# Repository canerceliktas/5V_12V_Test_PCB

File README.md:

# 5V_12V_Test_PCB
 Measuring the 2 inputs to detecting correct voltage values and show them on 7-Segment Display using a PIC16F876. It was a control card for measuring our custom design pcbs.

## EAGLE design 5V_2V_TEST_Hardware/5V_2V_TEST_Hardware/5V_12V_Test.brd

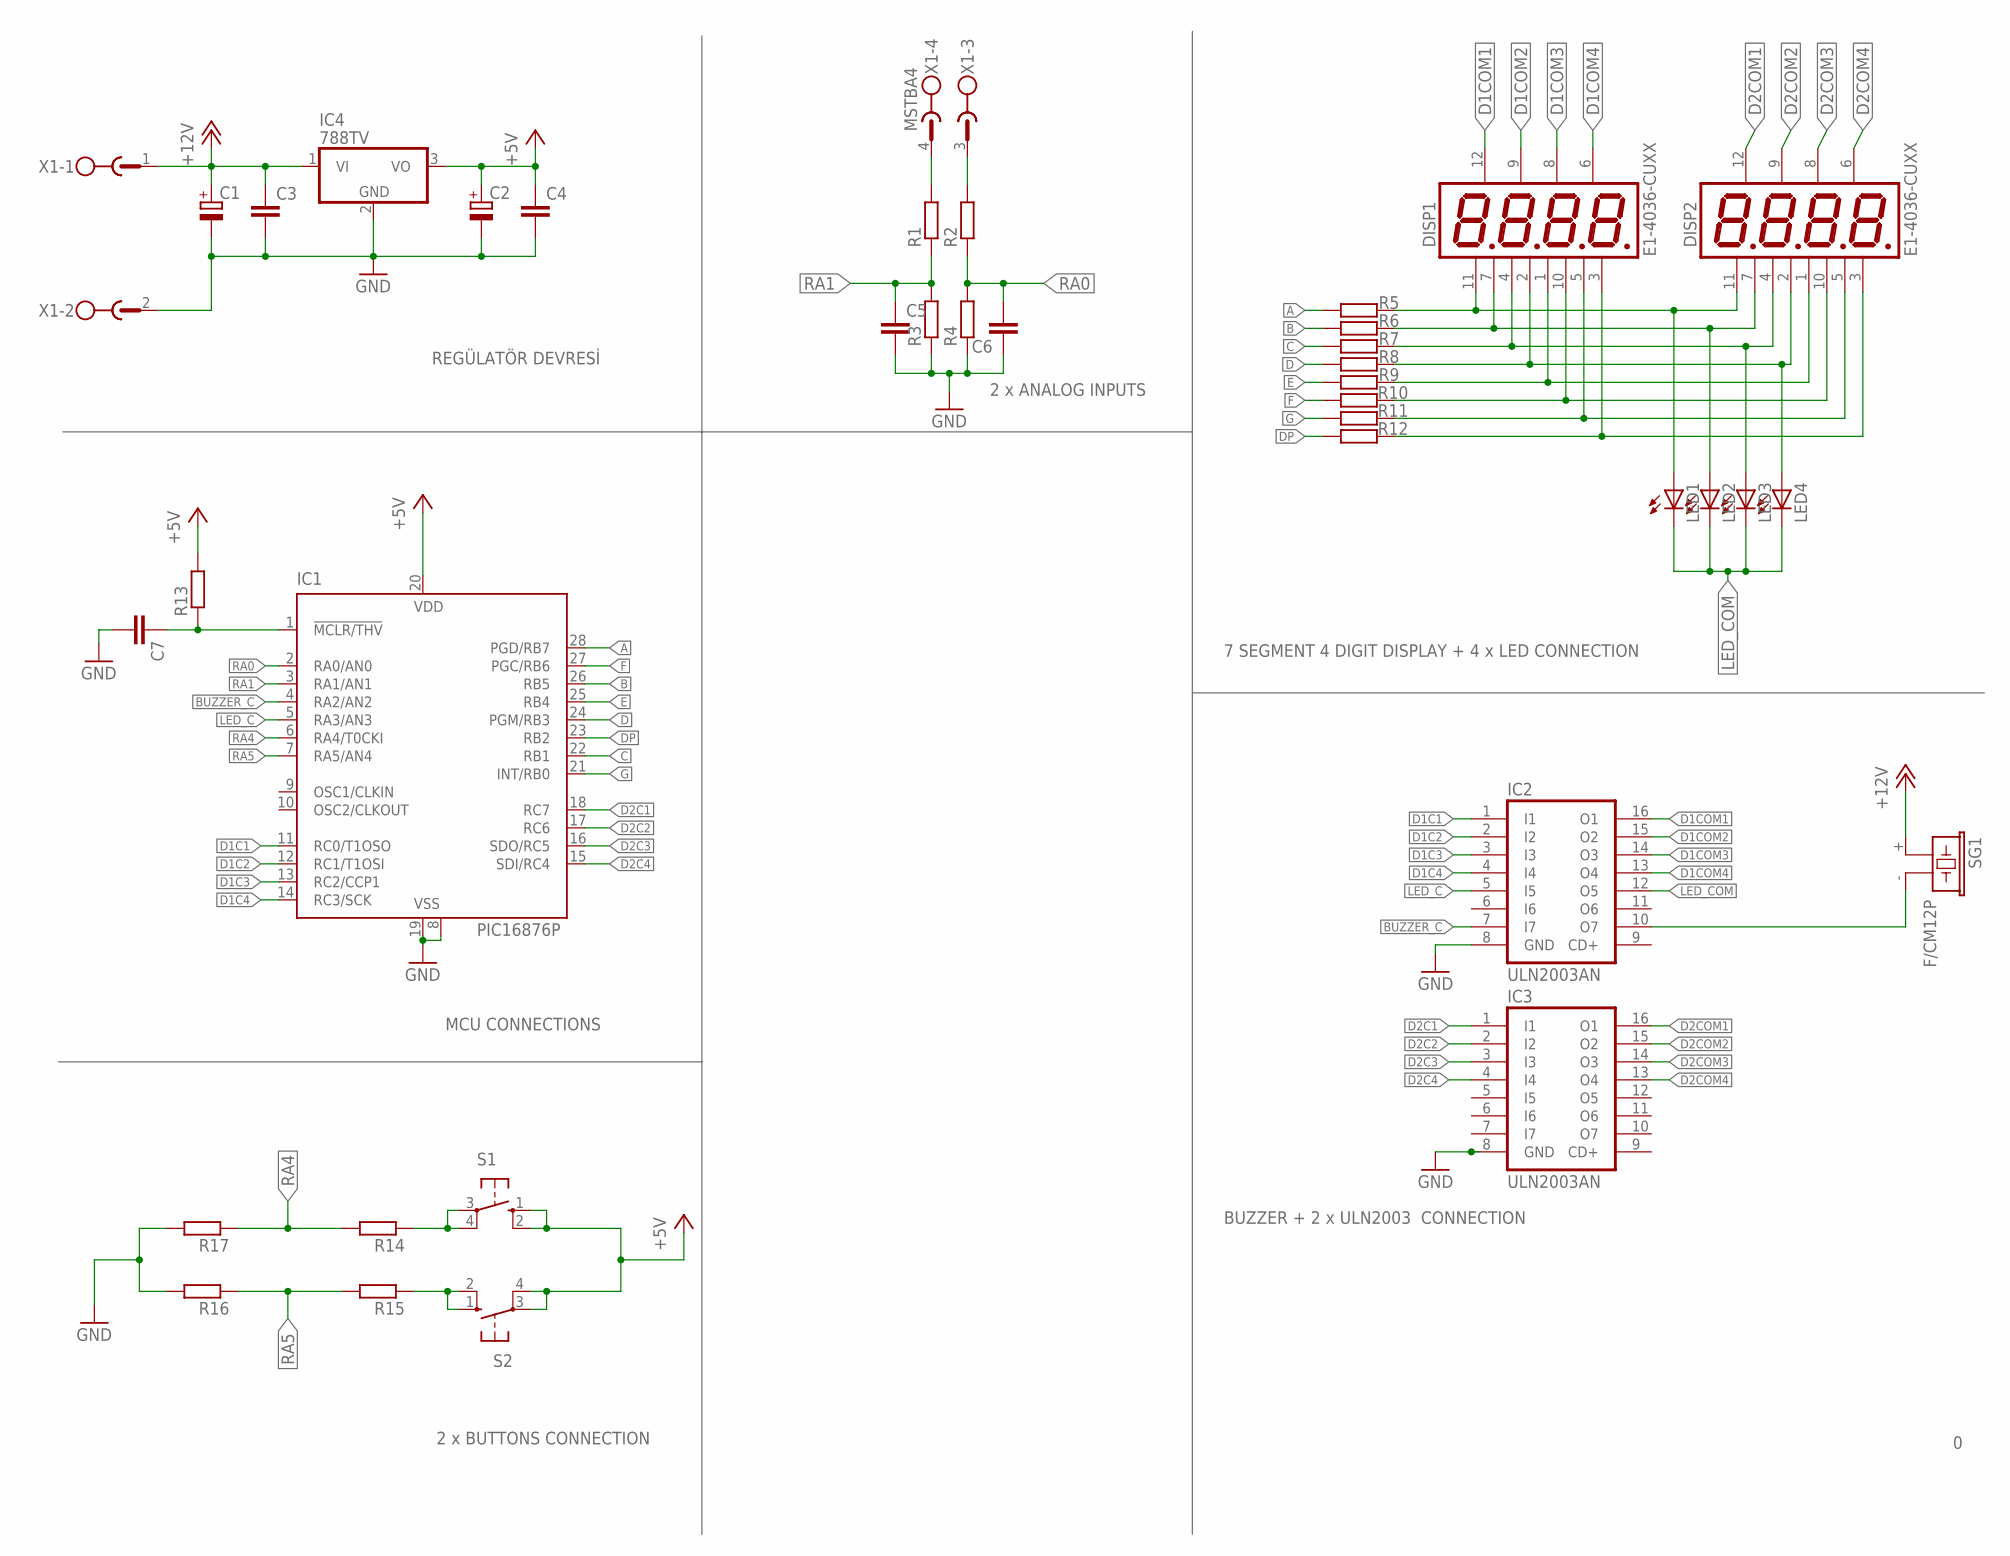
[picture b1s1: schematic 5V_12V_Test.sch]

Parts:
C1, C2: CPOL-EUE5-8.5; E5-8,5
C3, C4, C5, C6, C7: C-EU050-025X075; C050-025X075
DISP1, DISP2: E1-4036-CUXX
IC1: PIC16876P; DIL28-3
IC2, IC3: ULN2003AN; DIL16
IC4: 788TV; TO220V
LED1, LED2, LED3, LED4: LED5MM
R1, R2, R3, R4, R5, R6, R7, R8, R9, R10, R11, R12, R13, R14, R15, R16, R17: R-EU_0207/10; 0207/10
S1, S2: 10-XX; B3F-10XX
SG1: F/CM12P
X1: MSTBA4

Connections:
+5V: C2.+, C4.1, IC1.20 (VDD), IC4.3 (VO), R13.2, S1.1 (S), S1.2 (S1), S2.3, S2.4 (P1)
+12V: C1.+, C3.1, IC4.1 (VI), SG1.+ (1), X1.1
A: IC1.28 (PGD/RB7), R5.2
B: IC1.26 (RB5), R6.2
BUZZER_C: IC1.4 (RA2/AN2), IC2.7 (I7)
C: IC1.22 (RB1), R7.2
D: IC1.24 (PGM/RB3), R8.2
D1C1: IC1.11 (RC0/T1OSO), IC2.1 (I1)
D1C2: IC1.12 (RC1/T1OSI), IC2.2 (I2)
D1C3: IC1.13 (RC2/CCP1), IC2.3 (I3)
D1C4: IC1.14 (RC3/SCK), IC2.4 (I4)
D1COM1: DISP1.12 (DIG1), IC2.16 (O1)
D1COM2: DISP1.9 (DIG2), IC2.15 (O2)
D1COM3: DISP1.8 (DIG3), IC2.14 (O3)
D1COM4: DISP1.6 (DIG4), IC2.13 (O4)
D2C1: IC1.18 (RC7), IC3.1 (I1)
D2C2: IC1.17 (RC6), IC3.2 (I2)
D2C3: IC1.16 (SDO/RC5), IC3.3 (I3)
D2C4: IC1.15 (SDI/RC4), IC3.4 (I4)
D2COM1: DISP2.12 (DIG1), IC3.16 (O1)
D2COM2: DISP2.9 (DIG2), IC3.15 (O2)
D2COM3: DISP2.8 (DIG3), IC3.14 (O3)
D2COM4: DISP2.6 (DIG4), IC3.13 (O4)
DP: IC1.23 (RB2), R12.2
E: IC1.25 (RB4), R9.2
F: IC1.27 (PGC/RB6), R10.2
G: IC1.21 (INT/RB0), R11.2
GND: C1.-, C2.-, C3.2, C4.2, C5.2, C6.1, C7.2, IC1.8 (VSS), IC1.19 (VSS), IC2.8 (GND), IC3.8 (GND), IC4.2 (GND), R3.1, R4.1, R16.2, R17.2, X1.2
LED_C: IC1.5 (RA3/AN3), IC2.5 (I5)
LED_COM: IC2.12 (O5), LED1.K (C), LED2.K (C), LED3.K (C), LED4.K (C)
unnamed: DISP1.11 (A), DISP2.11 (A), LED1.A, R5.1
unnamed: DISP1.7 (B), DISP2.7 (B), LED2.A, R6.1
unnamed: DISP1.4 (C), DISP2.4 (C), LED3.A, R7.1
unnamed: DISP1.2 (D), DISP2.2 (D), LED4.A, R8.1
unnamed: DISP1.1 (E), DISP2.1 (E), R9.1
unnamed: R1.2, X1.4
unnamed: R2.2, X1.3
unnamed: DISP1.10 (F), DISP2.10 (F), R10.1
unnamed: DISP1.5 (G), DISP2.5 (G), R11.1
unnamed: DISP1.3 (DP), DISP2.3 (DP), R12.1
unnamed: C7.1, IC1.1 (!MCLR/THV), R13.1
unnamed: R14.1, S1.3, S1.4 (P1)
unnamed: R15.1, S2.1 (S), S2.2 (S1)
unnamed: IC2.10 (O7), SG1.- (2)
RA0: C6.2, IC1.2 (RA0/AN0), R2.1, R4.2
RA1: C5.1, IC1.3 (RA1/AN1), R1.1, R3.2
RA4: IC1.6 (RA4/T0CKI), R14.2, R17.1
RA5: IC1.7 (RA5/AN4), R15.2, R16.1

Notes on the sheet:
REGÜLATÖR DEVRESİ
2 x ANALOG INPUTS
7 SEGMENT 4 DIGIT DISPLAY + 4 x LED CONNECTION
BUZZER + 2 x ULN2003 CONNECTION
2 x BUTTONS CONNECTION
MCU CONNECTIONS

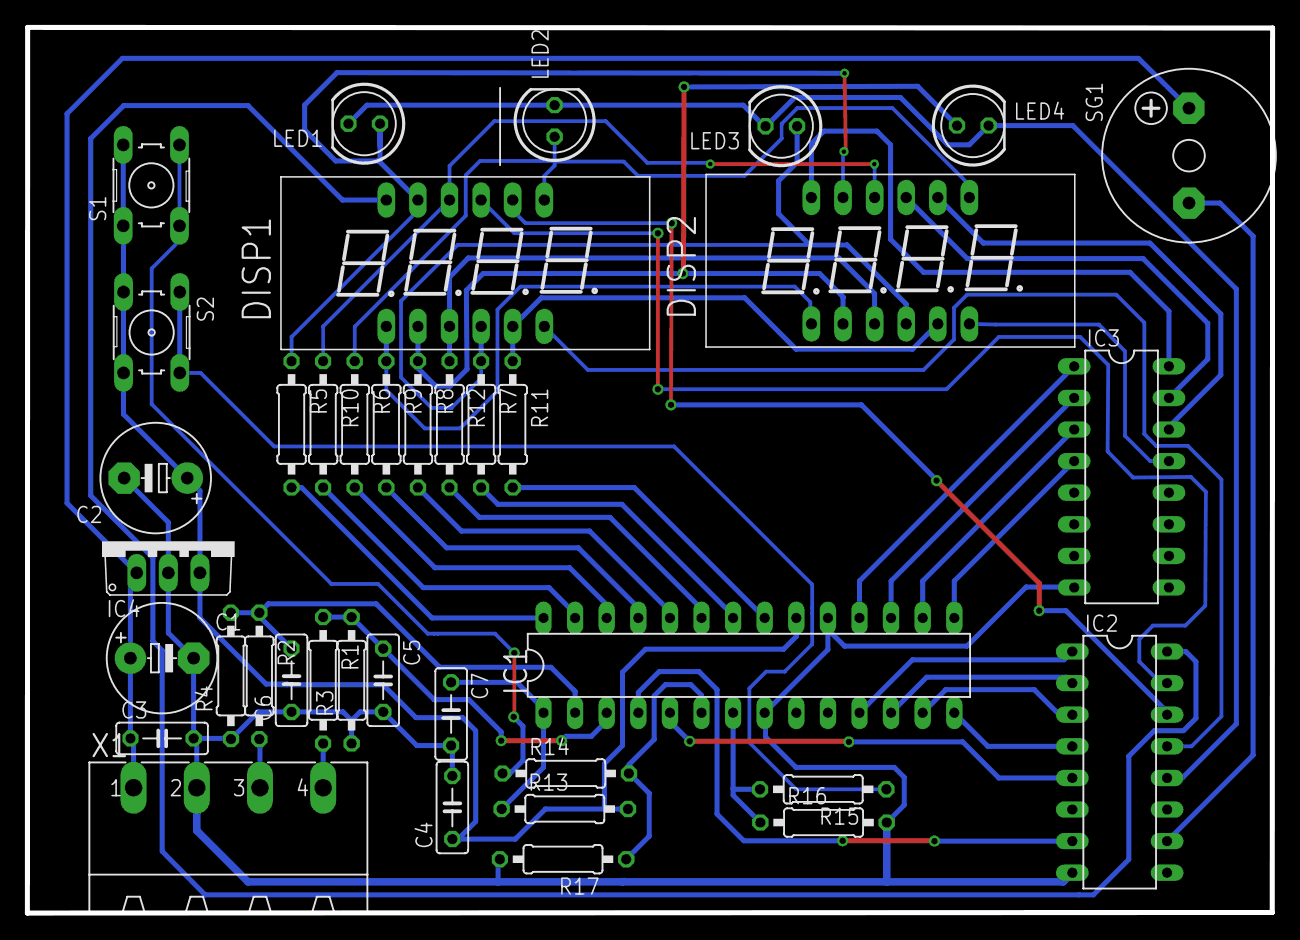
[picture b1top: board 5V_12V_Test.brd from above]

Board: 2 copper layers, 100.1 x 71.2 mm, 38 parts (0 on the bottom side), 48 nets.

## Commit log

2019-07-19 Code and PCB Design Added
2019-07-19 Name changed
